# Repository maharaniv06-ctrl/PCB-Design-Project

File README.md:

# PCB-Design-Project
This project designs a PCB for a complete signal-conditioning module that includes a bandpass filter, amplifier, and clipper. The circuit prepares raw sensor signals by filtering noise, boosting amplitude, and limiting peaks, enabling clean and stable input for further processing.

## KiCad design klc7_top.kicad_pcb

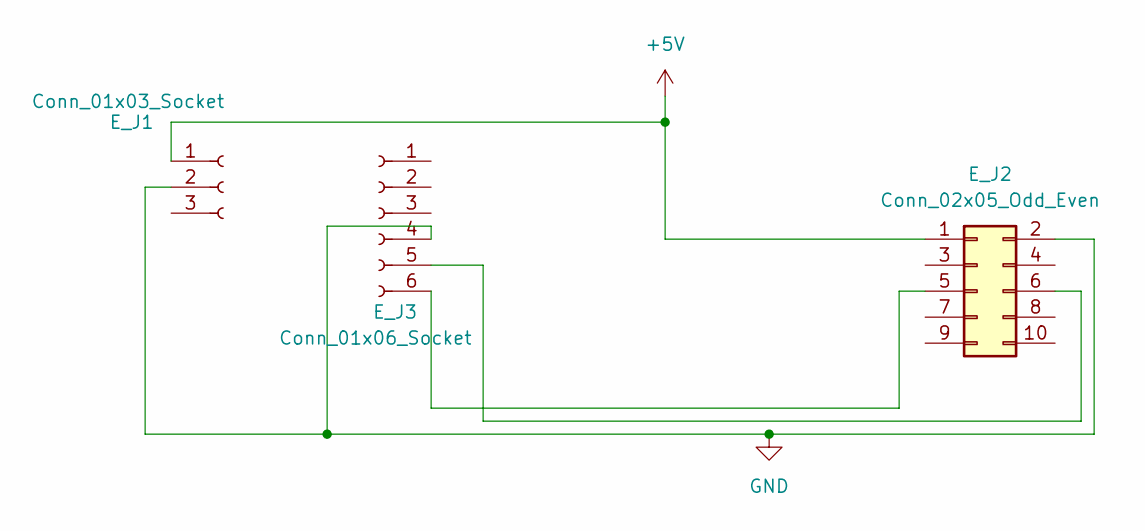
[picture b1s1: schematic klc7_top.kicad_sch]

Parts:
E_J1: Conn_01x03_Socket; PinHeader_1x03_P2.54mm_Vertical
E_J2: Conn_02x05_Odd_Even; IDC-Header_2x05_P2.54mm_Vertical
E_J3: Conn_01x06_Socket; PinSocket_1x06_P2.54mm_Vertical

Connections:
+5V: E_J1.1, E_J2.1
GND: E_J1.2, E_J2.2, E_J3.4
unnamed: E_J2.5, E_J3.6
unnamed: E_J2.6, E_J3.5

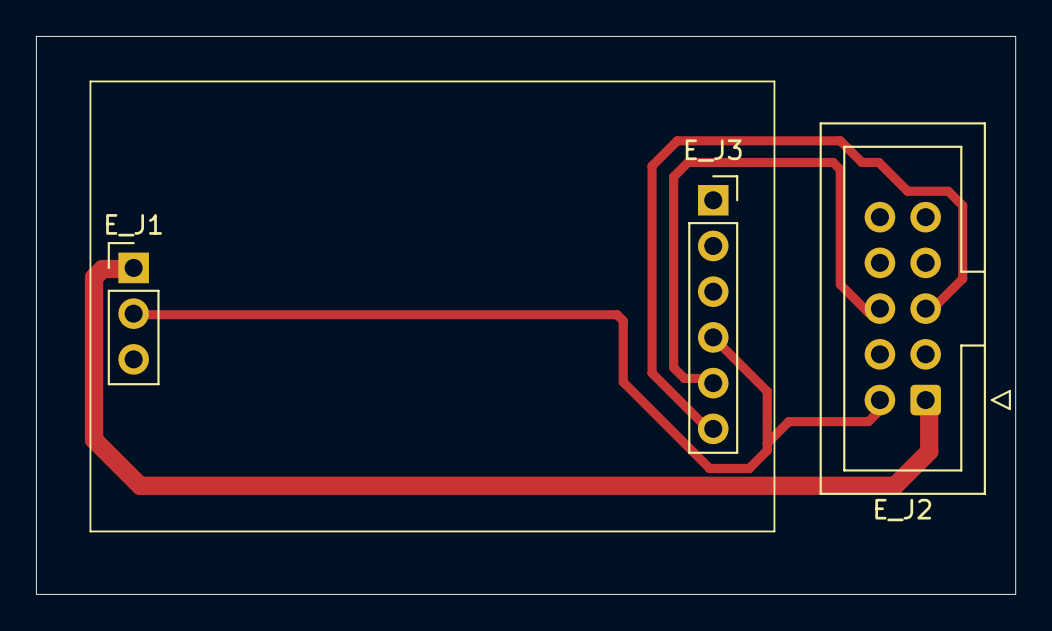
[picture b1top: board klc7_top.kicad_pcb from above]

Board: 2 copper layers, 54.4 x 31.0 mm, 3 parts (0 on the bottom side), 4 nets.

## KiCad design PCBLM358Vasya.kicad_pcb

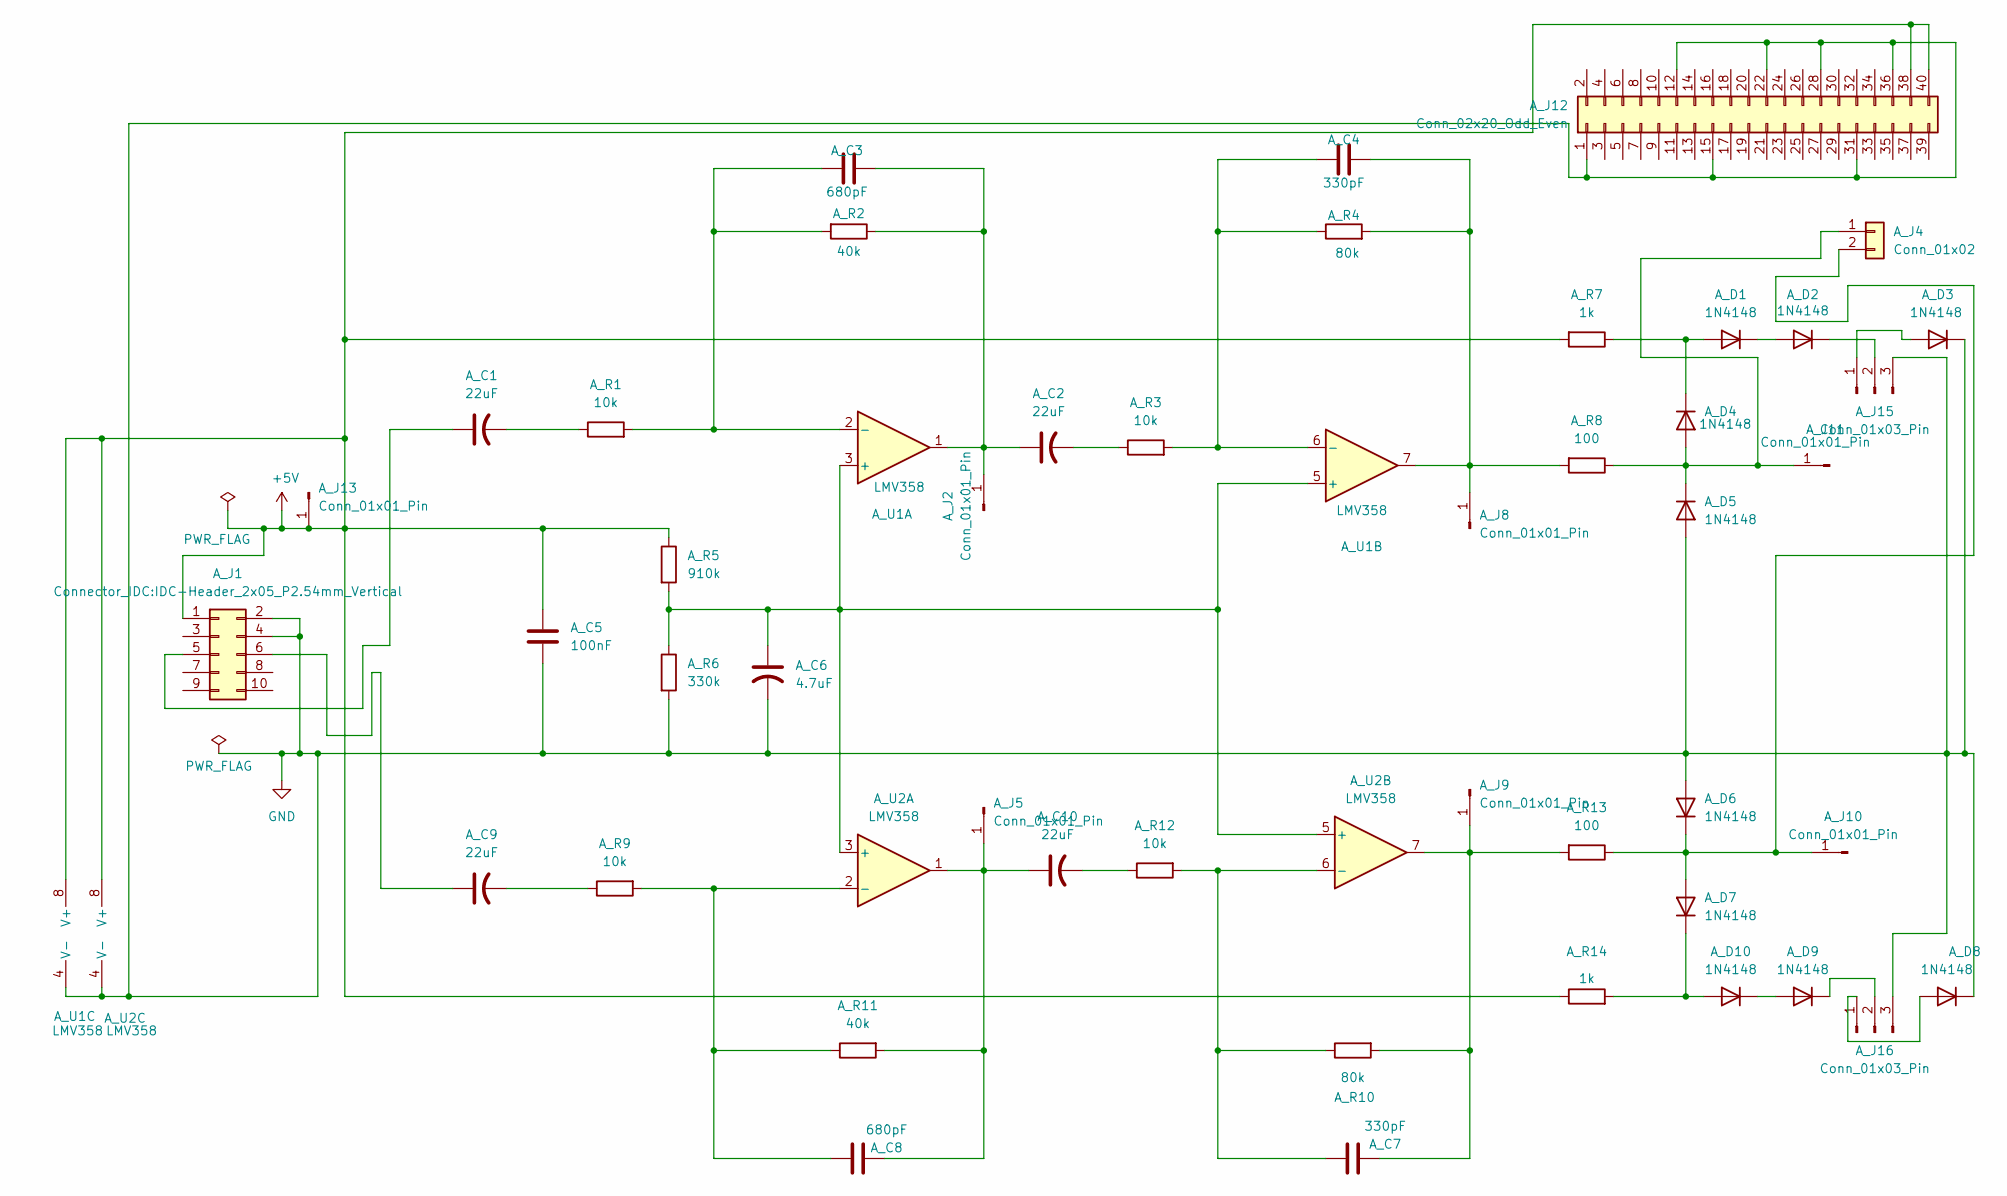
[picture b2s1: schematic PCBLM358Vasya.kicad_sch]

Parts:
A_C1, A_C2, A_C9, A_C10: 22uF; CP_Elec_6.3x7.7
A_C3, A_C8: 680pF; C_0805_2012Metric
A_C4, A_C7: 330pF; C_0805_2012Metric
A_C5: 100nF; C_0805_2012Metric
A_C6: 4.7uF; CP_Elec_4x5.4
A_D1, A_D2, A_D3, A_D4, A_D5, A_D6, A_D7, A_D8, A_D9, A_D10: 1N4148; D_SOD-123
A_J1: Connector_IDC:IDC-Header_2x05_P2.54mm_Vertical; IDC-Header_2x05_P2.54mm_Vertical
A_J2, A_J5, A_J8, A_J9, A_J10, A_J11, A_J13: Conn_01x01_Pin; PinHeader_1x01_P2.54mm_Vertical
A_J4: Conn_01x02; JST_EH_B2B-EH-A_1x02_P2.50mm_Vertical
A_J12: Conn_02x20_Odd_Even; MODULE_RASPBERRY_PI_ZERO_2_W
A_J15, A_J16: Conn_01x03_Pin; PinHeader_1x03_P2.54mm_Vertical
A_R1, A_R3, A_R9, A_R12: 10k; R_0805_2012Metric
A_R2, A_R11: 40k; R_0805_2012Metric
A_R4, A_R10: 80k; R_0805_2012Metric
A_R5: 910k; R_0805_2012Metric
A_R6: 330k; R_0805_2012Metric
A_R7, A_R14: 1k; R_0805_2012Metric
A_R8, A_R13: 100; R_0805_2012Metric
A_U1, A_U2: LMV358; SOIC-8_3.9x4.9mm_P1.27mm

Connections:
+5V: A_C5.1, A_J1.1, A_J12.38, A_J12.40, A_J13.1, A_R5.1, A_R7.2, A_R14.1, A_U1.8 (V+), A_U2.8 (V+)
GND: A_C5.2, A_C6.2, A_D3.1 (K), A_D5.2 (A), A_D6.2 (A), A_D8.1 (K), A_J1.2, A_J1.4, A_J12.1, A_J12.12, A_J12.15, A_J12.22, A_J12.28, A_J12.31, A_J12.36, A_J15.3, A_J16.3, A_R6.2, A_U1.4 (V-), A_U2.4 (V-)
unnamed: A_C1.2, A_R1.1
unnamed: A_C2.2, A_R3.1
unnamed: A_C9.2, A_R9.1
unnamed: A_C10.2, A_R12.1
unnamed: A_D1.2 (A), A_D4.1 (K), A_R7.1
unnamed: A_D1.1 (K), A_D2.2 (A)
unnamed: A_D2.1 (K), A_J15.2
unnamed: A_D3.2 (A), A_J15.1
unnamed: A_D4.2 (A), A_D5.1 (K), A_J4.1, A_J11.1, A_R8.1
unnamed: A_D6.1 (K), A_D7.2 (A), A_J4.2, A_J10.1, A_R13.1
unnamed: A_D8.2 (A), A_J16.1
unnamed: A_D9.1 (K), A_J16.2
unnamed: A_D7.1 (K), A_D10.2 (A), A_R14.2
unnamed: A_D9.2 (A), A_D10.1 (K)
unnamed: A_C1.1, A_J1.5
unnamed: A_C9.1, A_J1.6
unnamed: A_C2.1, A_C3.1, A_J2.1, A_R2.1, A_U1.1
unnamed: A_C8.2, A_C10.1, A_J5.1, A_R11.2, A_U2.1
unnamed: A_C4.2, A_J8.1, A_R4.2, A_R8.2, A_U1.7
unnamed: A_C7.2, A_J9.1, A_R10.2, A_R13.2, A_U2.7
unnamed: A_C6.1, A_R5.2, A_R6.1, A_U1.3 (+), A_U1.5 (+), A_U2.3 (+), A_U2.5 (+)
unnamed: A_C3.2, A_R1.2, A_R2.2, A_U1.2 (-)
unnamed: A_C4.1, A_R3.2, A_R4.1, A_U1.6 (-)
unnamed: A_C8.1, A_R9.2, A_R11.1, A_U2.2 (-)
unnamed: A_C7.1, A_R10.1, A_R12.2, A_U2.6 (-)

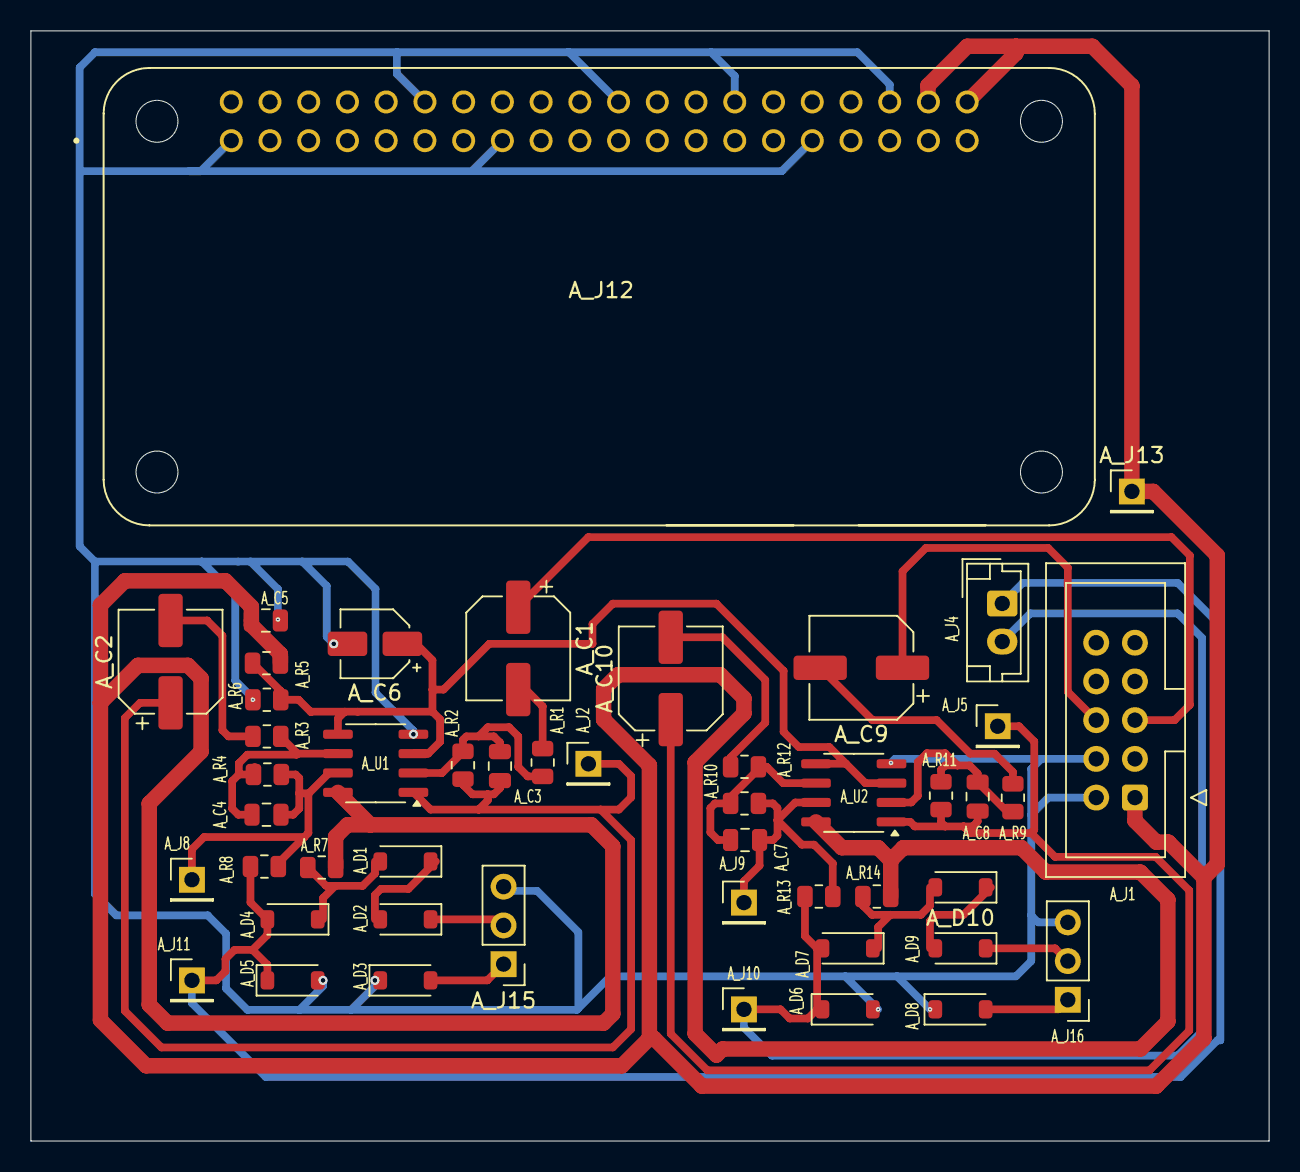
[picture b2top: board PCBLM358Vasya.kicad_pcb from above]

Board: 2 copper layers, 81.2 x 72.8 mm, 48 parts (0 on the bottom side), 27 nets.
